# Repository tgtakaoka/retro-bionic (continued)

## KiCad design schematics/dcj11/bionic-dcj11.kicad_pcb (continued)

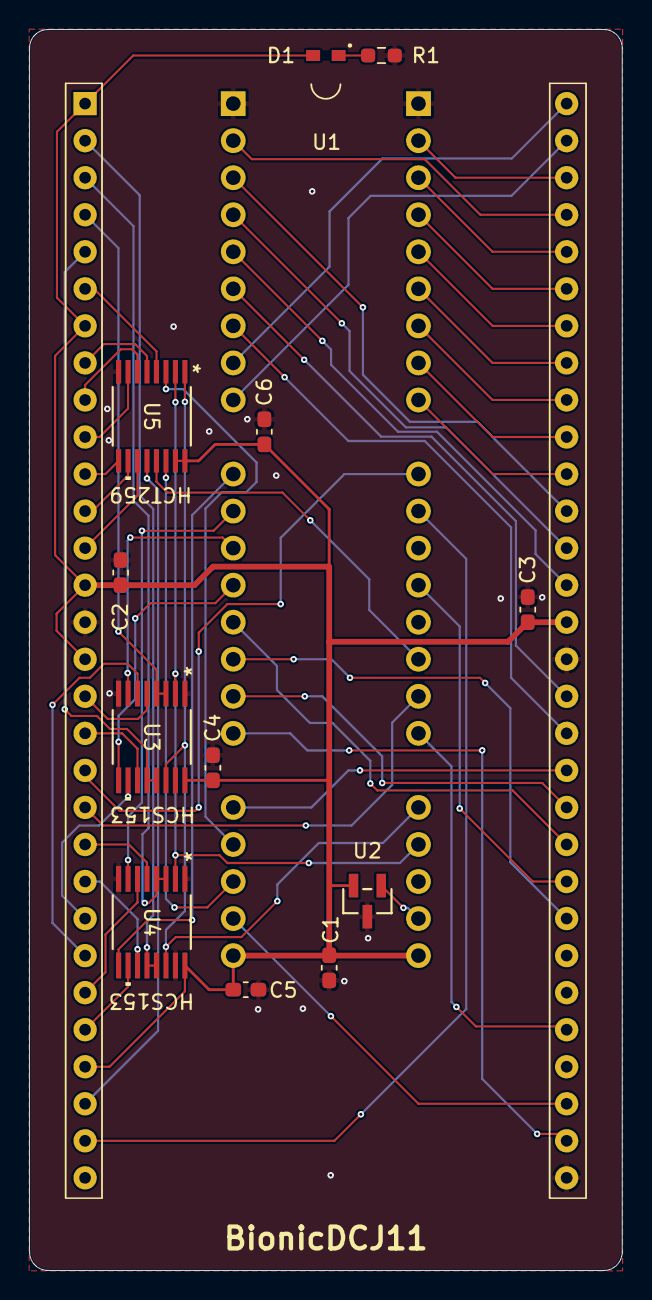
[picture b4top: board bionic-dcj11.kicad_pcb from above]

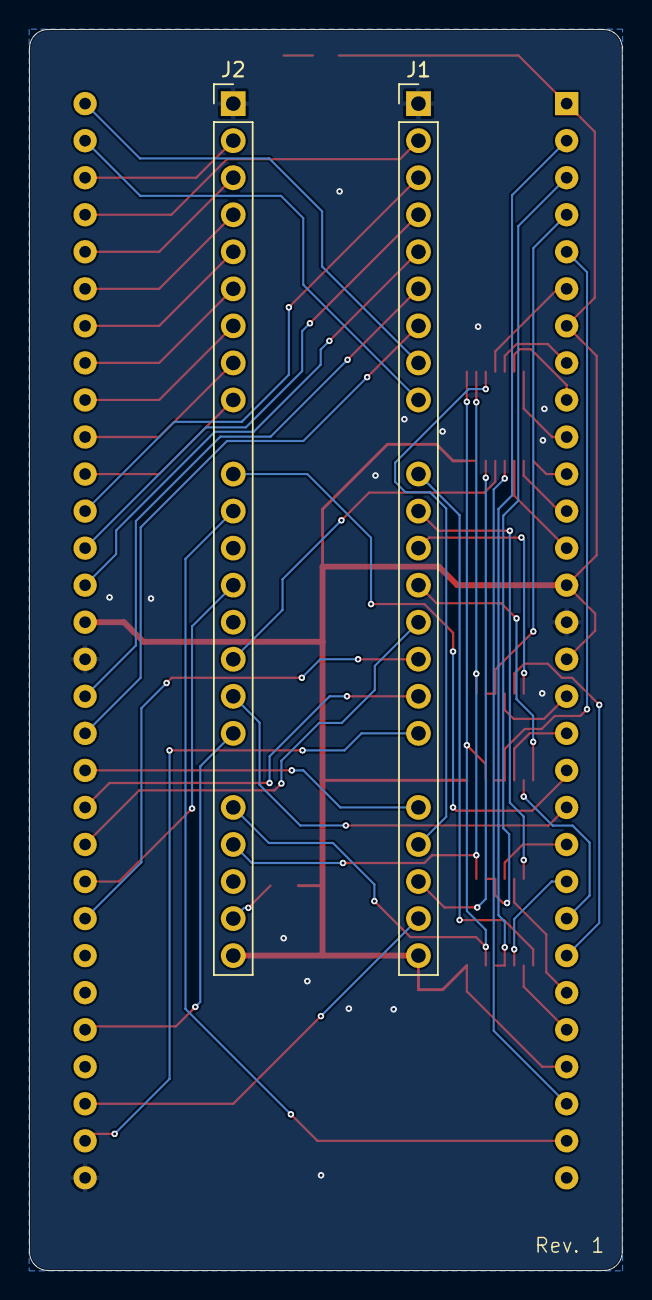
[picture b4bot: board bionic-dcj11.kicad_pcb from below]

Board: 2 copper layers, 40.6 x 85.1 mm, 15 parts (2 on the bottom side), 60 nets.

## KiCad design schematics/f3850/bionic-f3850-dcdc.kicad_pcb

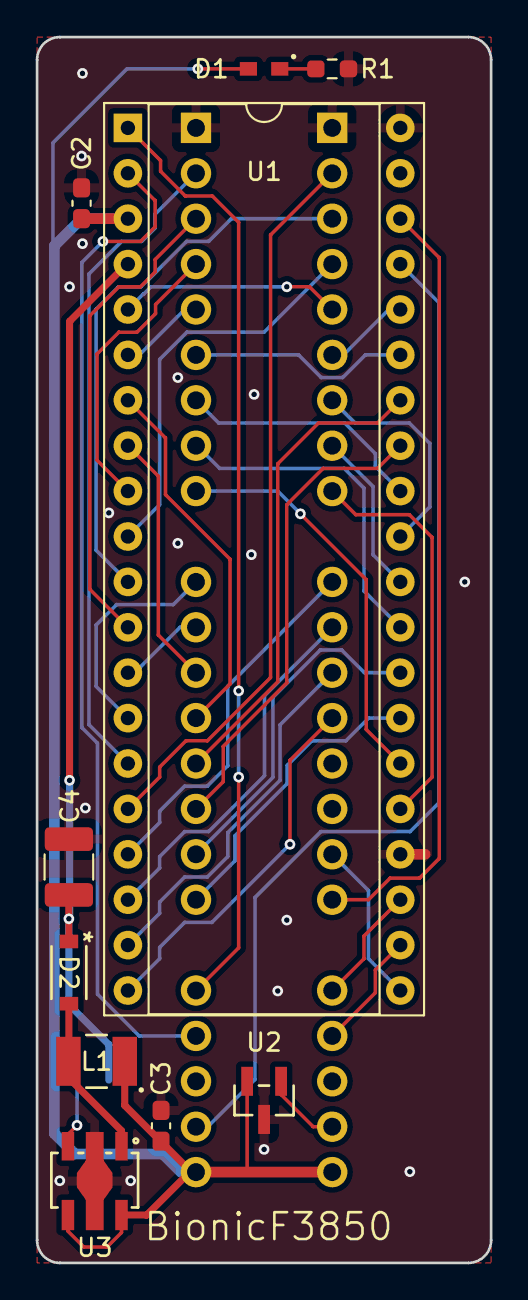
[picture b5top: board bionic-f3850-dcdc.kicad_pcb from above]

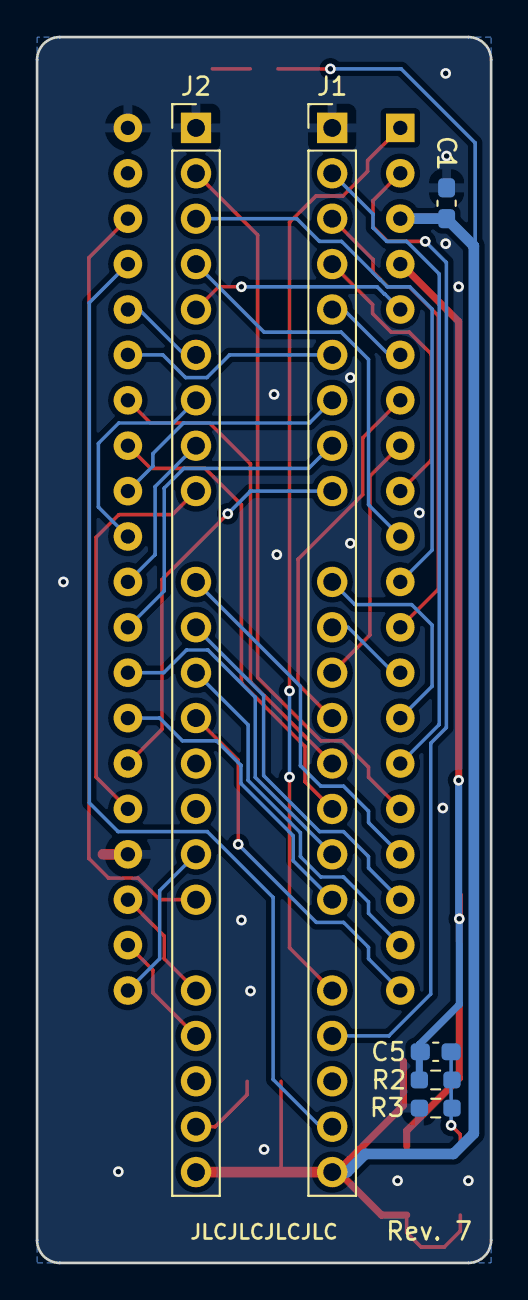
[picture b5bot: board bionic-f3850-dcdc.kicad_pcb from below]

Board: 2 copper layers, 25.4 x 68.6 mm, 16 parts (6 on the bottom side), 42 nets.

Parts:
C1: 22u; C_0603_1608Metric_Pad1.08x0.95mm_HandSolder
C2: 0.1u; C_0603_1608Metric_Pad1.08x0.95mm_HandSolder
C3: 10uF/50V; C_0603_1608Metric_Pad1.08x0.95mm_HandSolder
C4: 22uF/16V; C_1210_3225Metric_Pad1.33x2.70mm_HandSolder
C5: 15pF; C_0603_1608Metric_Pad1.08x0.95mm_HandSolder
D1: CSL1901UW1; LED_CSL1901UW1_ROM-M
D2: 30V/1A; CR_60M-60_ROM-M
J1: Bionic-P135; Bionic-P135_Vertical
J2: Bionic-P245; Bionic-P245_Vertical
L1: 10uH/3A; IND_DFE322512F_MUR-M
R1: 1.6k; R_0603_1608Metric_Pad0.98x0.95mm_HandSolder
R2: 220k; R_0603_1608Metric_Pad0.98x0.95mm_HandSolder
R3: 20k; R_0603_1608Metric_Pad0.98x0.95mm_HandSolder
U1: F3850; DIP-40_W15.24mm_Socket
U2: 11AA010-I/TT; SOT-23_MC_MCH-M
U3: NJW4132; SOT-89-5_NMD-M

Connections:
/P10: J1.2 (P10), U1.15 (DB0)
/P11: J1.3 (P11), U1.12 (DB1)
/P12: J1.4 (P12), U1.9 (DB2)
/P13: J1.5 (P13), U1.6 (DB3)
/P14: J1.6 (P14), U1.35 (DB4)
/P15: J1.7 (P15), U1.32 (DB5)
/P16: J1.8 (P16), U1.29 (DB6)
/P17: J1.9 (P17), U1.26 (DB7)
/P20: J2.47 (P20), U1.16 (~IO00)
/P21: J2.46 (P21), U1.11 (~IO01)
/P22: J2.45 (P22), U1.10 (~IO02)
/P23: J2.44 (P23), U1.5 (~IO03)
/P24: J2.43 (P24), U1.36 (~IO04)
/P25: J2.42 (P25), U1.31 (~IO05)
/P26: J2.41 (P26), U1.30 (~IO06)
/P27: J2.40 (P27), U1.25 (~IO07)
/P30: J1.11 (P30), U1.14 (~IO10)
/P31: J1.12 (P31), U1.13 (~IO11)
/P32: J1.13 (P32), U1.8 (~IO12)
/P33: J1.14 (P33), U1.7 (~IO13)
/P34: J1.15 (P34), U1.34 (~IO14)
/P35: J1.16 (P35), U1.33 (~IO15)
/P36: J1.17 (P36), U1.28 (~IO16)
/P37: J1.18 (P37), U1.27 (~IO17)
/P40: J2.38 (P40), U1.17 (ROMC0)
/P41: J2.37 (P41), U1.18 (ROMC1)
/P42: J2.36 (P42), U1.19 (ROMC2)
/P43: J2.35 (P43), U1.20 (ROMC3)
/P46: J2.32 (P46), U1.21 (ROMC4)
/P47: J2.31 (P47), U1.38 (XTLY)
/P50: J1.20 (P50), U1.1 (PHI)
/P51: J1.21 (P51), U1.2 (WRITE)
/P53: J1.23 (P53), U1.37 (~EXTRES)
/P54: J2.29 (P54), U1.23 (~INTREQ)
/P55: J2.28 (P55), U1.22 (~ICB)
/dcdc+12v/+12V: C4.1, C5.1, D2.1 (K), R2.1, U1.4 (VGG)
GND: C1.2, C2.2, C3.2, C4.2, J1.1 (GND), J2.48 (GND), R1.2, R3.2, U1.24 (VSS), U1.40 (XTLZ), U2.3 (VSS), U3.2 (GND)
unnamed: D1.1 (K), R1.1
unnamed: D2.2 (A), L1.2, U3.1 (SW)
unnamed: J2.26 (P57), U2.1 (SCIO)
unnamed: C5.2, R2.2, R3.1, U3.3 (IN-)
VCC: C1.1, C2.1, C3.1, D1.2 (A), J1.24 (VCC), J2.25 (VCC), L1.1, U1.3 (VDD), U2.2 (VCC), U3.4 (EN), U3.5 (V+)
